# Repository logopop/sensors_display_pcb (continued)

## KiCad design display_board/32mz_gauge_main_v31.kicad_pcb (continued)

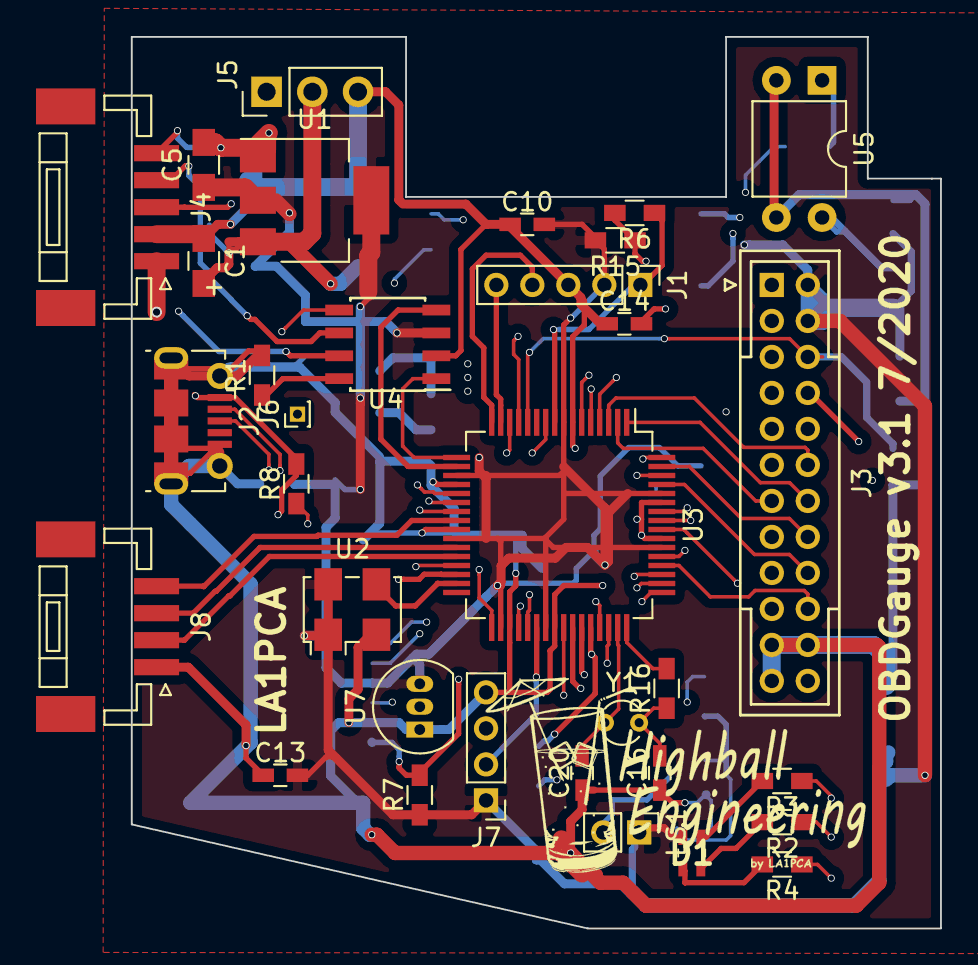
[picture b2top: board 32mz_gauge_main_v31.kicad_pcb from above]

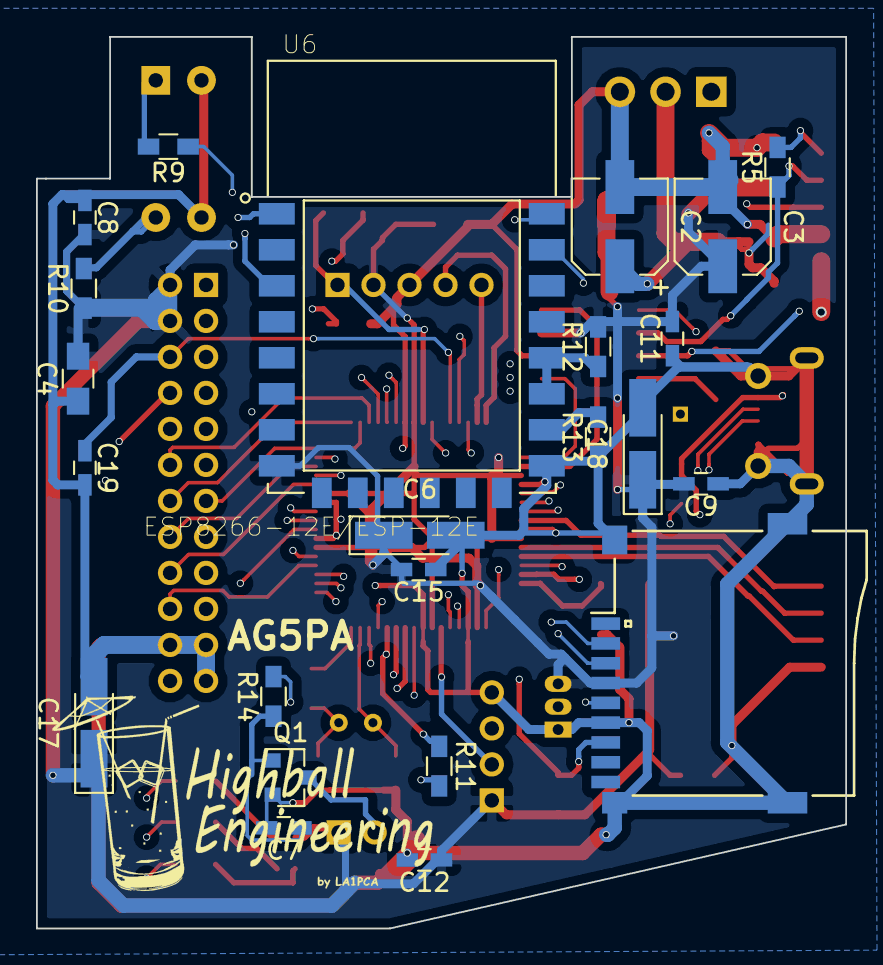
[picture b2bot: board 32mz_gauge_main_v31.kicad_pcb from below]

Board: 4 copper layers, 45.0 x 49.5 mm, 56 parts (23 on the bottom side), 67 nets.

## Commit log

2022-08-29 Initial commit
    SCH, PCB, and Gerbers for both the display and sensor boards.
